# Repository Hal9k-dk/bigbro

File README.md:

# BigBro

BigBro is the system used by Hal9K to control access to its different advanced
machines, with RFID based access control.

The system is designed to cut power to the machines if no valid key-card is present
or in the special case of a 3D printer, if no special key-card is present, 
and a print isn't ongoing.

The first version of BigBro was designed around the ESP8266, specifically the WEMOS D1 mini.
Version 2 uses ESP32 with the [EspressIf ESP-IDF](https://idf.espressif.com/).

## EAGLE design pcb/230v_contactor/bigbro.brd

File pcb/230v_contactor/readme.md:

# Contactor PCB
PCB design for the normal big-bro access boxes, meant to control a 230v contactor.

Eagle version 7.2.0

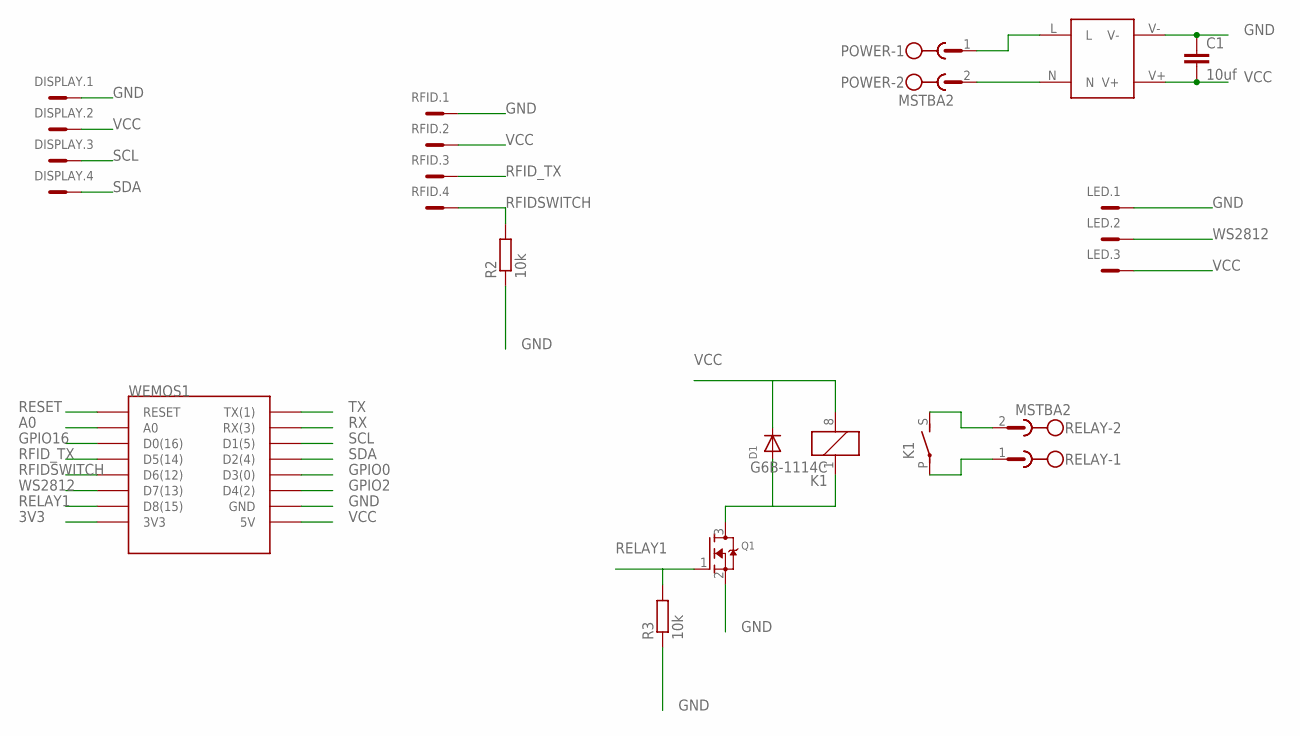
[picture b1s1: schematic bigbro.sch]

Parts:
C1: 10uf; C0805
D1: DIODESMA; SMADIODE
DISPLAY: MC4
K1: G6B-1114C
LED: MC3
POWER: MSTBA2
Q1: MOSFET-NREFLOW; SOT23
R2, R3: 10k; M0805
RELAY: MSTBA2
RFID: MC4
U$1: HLK-PM03
WEMOS1: WEMOS-D1-MINI

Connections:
3V3: WEMOS1.3V3
A0: WEMOS1.A0
GND: C1.1, DISPLAY.1, LED.1, Q1.2 (S), R2.1, R3.1, RFID.1, U$1.V-, WEMOS1.GND
GPIO0: WEMOS1.D3 (D3(0))
GPIO2: WEMOS1.D4 (D4(2))
GPIO16: WEMOS1.D0 (D0(16))
unnamed: POWER.1, U$1.L
unnamed: POWER.2, U$1.N
unnamed: K1.S, RELAY.2
unnamed: K1.P, RELAY.1
unnamed: D1.A, K1.1, Q1.3 (D)
RELAY1: Q1.1 (G), R3.2, WEMOS1.D8 (D8(15))
RESET: WEMOS1.RESET
RFIDSWITCH: R2.2, RFID.4, WEMOS1.D6 (D6(12))
RFID_TX: RFID.3, WEMOS1.D5 (D5(14))
RX: WEMOS1.RX (RX(3))
SCL: DISPLAY.3, WEMOS1.D1 (D1(5))
SDA: DISPLAY.4, WEMOS1.D2 (D2(4))
TX: WEMOS1.TX (TX(1))
VCC: C1.2, D1.C, DISPLAY.2, K1.8 (2), LED.3, RFID.2, U$1.V+, WEMOS1.5V
WS2812: LED.2, WEMOS1.D7 (D7(13))

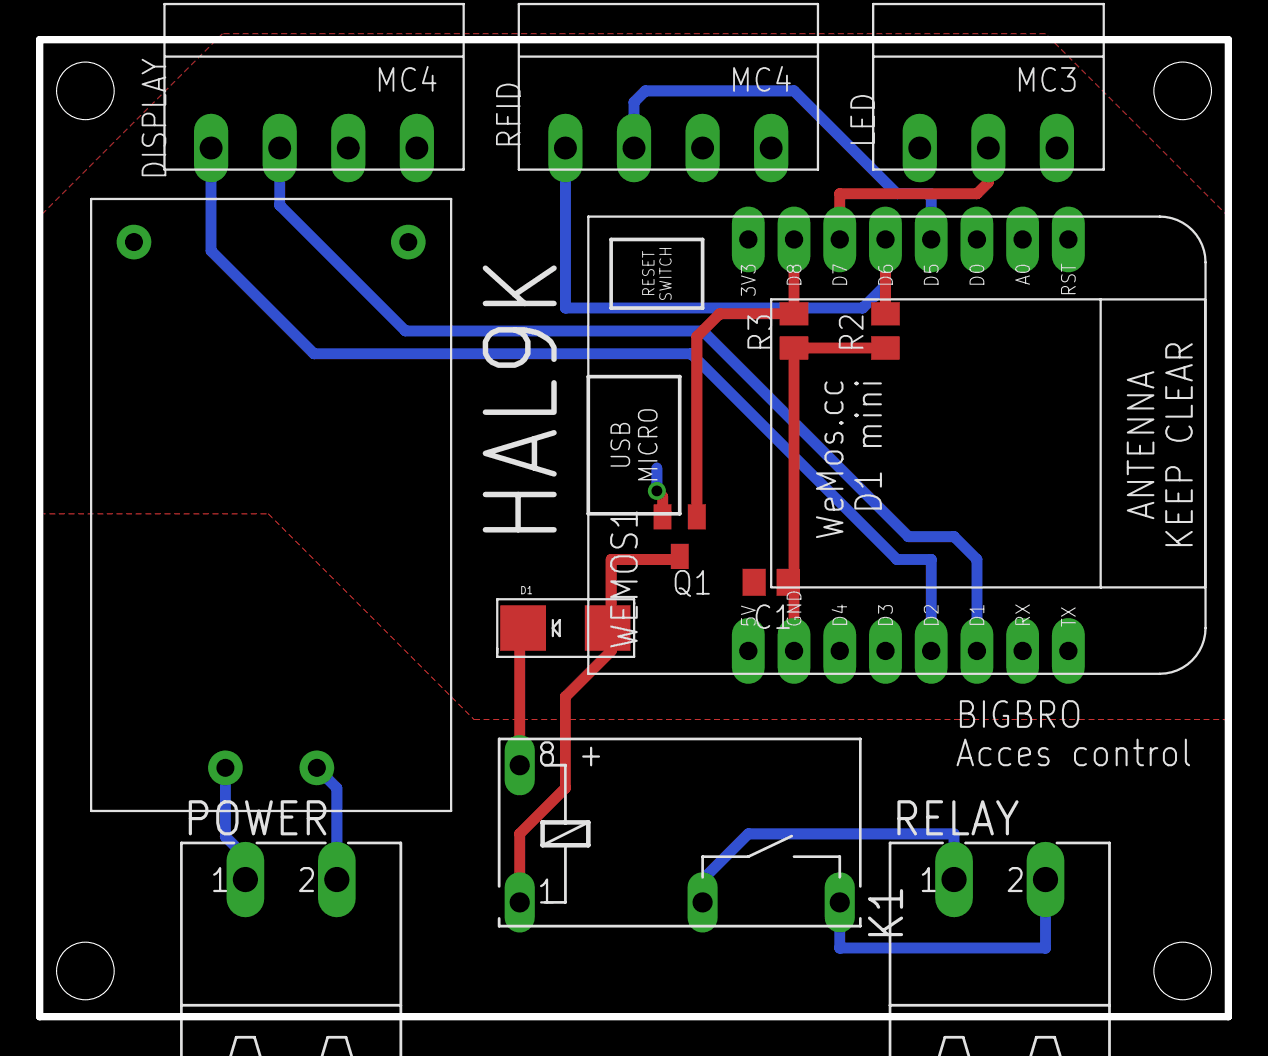
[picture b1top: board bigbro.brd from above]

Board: 2 copper layers, 66.0 x 54.3 mm, 13 parts (0 on the bottom side), 13 nets.

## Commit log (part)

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2018-09-15 firmware is currently weirdly broken
2018-09-15 First encounter of issues
2018-09-15 Further reduced complexity to get no interrupts
2018-09-16 further reduced test
2018-09-22 Changed tx pin to unused, as it is
2018-09-22 fixed current init
2018-09-22 More friendly screen
2018-09-23 Only check cards, not empty, for permission
2018-09-25 Streamlined wifi serial UI
2018-09-25 moved includes to header, added testing IP flag
2018-09-25 Moved to average of p2p current reading
2018-09-25 Added aditional input checks to wifi deltion
2018-09-25 minor changes
2018-09-25 Changed version to version 0.2.0
2018-09-27 enable travis ci
2018-09-27 Added newline after badge
2018-09-27 changed .travis.yml
2018-09-29 Began adding documentation
    Added doxygen config file.
    Documented main.cpp and base.h.
2018-09-29 Removed old .travis.yml
2018-09-29 Fixed Travis CI badge
    Capitalized read me file name.
2018-09-30 Added a bit of delay to show error messages on display
2018-09-30 Enabled more compiler warnings
2018-09-30 Moved flag test into header
2018-09-30 Removed averaging of current, reduced threshhold to 50mA
2018-09-30 Fixed lib_deps error
2018-10-18 Added threshhold for Ultimaker and TAZ
2018-10-18 Shit is broke
2018-10-18 made a temporary always on hack untill we can fix the stuff
2018-10-19 Revert "Shit is broke"
    This reverts commit e61f9288106303296d63b82bd6558d5188ae119d.
2018-10-19 Revert "Added threshhold for Ultimaker and TAZ"
    This reverts commit 2d10c56e86b93f1f911e7a29bbcce90c5f9df7a9.
2018-10-19 Made status line selection 0 indexed
2018-10-19 Cleaned up display, fixed inrush-current state change
2018-10-19 Incremented version, added options to dissable/enable ota
2018-10-19 Changed password for ota
2018-10-19 Increased cooldown to 9 minutes. Dissabled OTA during prints and cooldown
2018-10-19 something
2018-10-25 Fix UTF-8 display.
2018-10-31 Merged Access-System repo, into bigbro
2018-10-31 Fixed power-monitor PCB, to match real-life fixes
2018-12-10 made a state_change function to change state
2018-12-10 stored current_user_id
2018-12-10 Removed unused functions
2019-03-07 Worked on issue 8, pinned ArduinoJson to v5
2019-03-07 changed submodule to fork
2019-03-07 Implemented issue 8 fix
2019-03-07 Change to new submodule
2019-03-08 Made some values more human readable
2019-03-08 Merged changes from issue8 branch
2019-03-09 added threshhold configuration to platformio.ini
2019-03-09 Added "last user" field to eeprom
2019-03-09 made name_trunc a protected global. Cleaned up includes
2019-03-09 cleaned up includes
2019-03-09 made a "state_change" function to handle state changes
2019-03-09 Fixed potential EEPROM overflow issue
2019-03-09 Updated power_monitor pcb to use IRM-02 PSU
2019-03-09 Added folder for other PCB design
2019-03-09 Eagle files uploaded
2019-03-10 Pinned all libraries to major revision
2019-03-11 Removed submodule
2019-03-11 Moved to using PIO library for restclient
2019-03-13 Fixed library name
2019-03-13 Added build-flag to disable OTA, set SERIAL_DBG to 0 as default
2019-03-13 Trying to run CI on all controller types
2019-03-13 Set run to verbose for this test
2019-03-13 Added pragmas
2019-03-13 Added more pragma
2019-03-13 Disabled verbose output
2019-03-13 Only build platformio, and cancel builds if only docs changed
2019-03-13 Changed doc file to check new travis script
2019-03-13 Fixed spelling mistake
2019-03-15 added "clear" function Sets buffer to threshhold. So any new readings either screw the average up or down.
2019-03-15 Changed threshhold fr the UM
2019-03-15 Fixed printer thinking it was printing for the first minute
2019-03-15 Added super verbose serial dbg
2019-03-15 Set ota pwd to default. OTA will be disabled in production units
2019-03-15 Fixed inrush prevention function
2019-03-15 Finished up new printer code
2019-03-19 Documented Printer and ACS class
2019-03-19 Set up automated doxygen build and deployment to gh-pages
2019-03-19 Moved to much cleaner documentation generation
2019-03-19 fixed deployment branch
2019-03-19 Implemented main page for doxygen
2019-03-19 Updated main page formatting
2019-03-19 Fixed some variable descriptions
2019-03-19 More documentation
2019-03-20 Moved to single 'set_lines' function in display class
2019-09-05 A lot of stuff I can't remember, and fastled rate limit
2019-10-25 Cleanup.
2019-10-25 Bump REST client version.
2019-10-28 Add debug functions, fix peak-to-peak calculation.
2019-10-28 Add debug.
2019-10-28 Revert debug.
2019-11-28 Clear status when card is removed.
2019-11-28 while -> if
2020-01-30 Reduce debug noise.
2020-02-06 Untabify.
2020-02-06 Add lots of info in the display, make a bunch of gratuitous changes.
2020-02-06 Fix conflicts.
2020-02-06 Deploy Hal9k-dk/bigbro to github.com/Hal9k-dk/bigbro.git:gh-pages
2021-10-11 Added v2 schematic
2021-10-11 Added resistive divider to RX0
2021-10-17 Moved to SPDT relay, added 24pin FPC for e-ink
2021-10-17 Widened isolation slot
2021-10-21 Order1
2022-09-01 Add files via upload
    var begyndt på skift til andet display 1,44"
    https://www.aliexpress.com/item/4000219159401.html?spm=a2g0o.order_list.0.0.4b8d1802SihISr
2023-03-23 Add from zip file.
2023-03-30 Remove unneeded pulldown.
2023-04-01 Add local libs/footprints. Add GND testpoint.
2023-04-01 Update README for V2.
2023-04-01 Change to RDM6300, etc.
2023-04-02 New fuse holder, rearrange footprints.
2023-04-02 Optimize allocation of gates.
2023-04-02 Change current sense to single pin.
2023-04-03 Add 3D model for RDM6300 socket.
2023-04-03 Add 3D model for fuse holder.
2023-04-03 Route flip-flop, reduce width to 100 mm.
2023-04-03 Finish routing.
2023-04-03 Add extension connector.
2023-04-03 Fill zones.
2023-04-04 Remove solder mask on high-current traces.
2023-04-04 Add 3D model.
2023-04-04 Clarify connector labels.
2023-04-04 Order.
2023-05-06 Improve debug connector labels.
2023-05-06 Move display backlight from GPIO12 to GPIO14 to fix boot problem.
2023-05-06 Add reset and boot switches.
2023-05-06 Add ESP32 skeleton code.
2023-05-06 Add console interface.
2023-05-06 Add voltage divider for RFID.
2023-05-06 Increase value of switch LED resistor.
2023-05-06 Add command to read switch; initialize switch GPIO.
2023-05-13 Add simple HW test program.
2023-05-13 Add symbolic names.
2023-05-13 Use RDM6300 protocol.
2023-05-13 Make rfid command work.
2023-05-13 Add RFID pin.
2023-05-13 Add delay.
2023-05-13 Enable display CS.
2023-05-13 Flip display connector.
2023-05-14 Swap S and D on Q3.
2023-05-14 Forgot to save
2023-05-15 Connect to WiFi.
2023-05-18 Make WiFi code work.
2023-06-01 PoC for coil holder.
2023-06-01 PoC for switch holder.
2023-06-02 Adjust to fit.
2023-06-03 Adjust.
2023-06-15 Fix Q3 footprint, Q4 resistor values.
2023-06-15 Use PWM for display backlight.
2023-06-17 Tweak.
2023-06-17 Control backlight manually.
2023-06-28 Add case front.
2023-07-02 Achieve perfection.
2023-07-02 First attempt of front.
2023-07-03 Enlarge card pocket slightly.
2023-07-03 First attempt.
2023-07-03 Fix bugs.
2023-07-04 Increase width of switch opening.
2023-07-04 Basic bottom.
2023-07-04 Add PCB standoffs.
2024-02-04 Tweak; add wall fittings.
2024-02-04 Update ESP-IDF.
2024-02-04 Move.
2024-02-04 Remove old OpenSCAD files.
2024-02-05 Remove unused function.
2024-02-05 Tweak insert hole.
2024-02-09 Fix display clip position.
2024-02-09 Make display retainers a bit smaller.
2024-02-14 Copy lots of stuff from ACS frontend.
2024-02-14 Add more test commands.
2024-02-16 Add GW credentials.
2024-02-17 Implement controller FSA.
2024-02-17 Start implementing display class.
2024-02-19 Switch to new display driver.
2024-02-20 More work on display class.
2024-02-24 Finish basic display functionality.
2024-02-25 Fix bug where first progress line was lost.
2024-02-25 Turn backlight on.
2024-02-25 Fix backlight config.
2024-02-25 Implement time display.
2024-03-15 Fix time display.
2024-03-16 Work on controller logic.
2024-03-16 Fix display bugs.
2024-03-16 Always trust the cache.
2024-03-16 Show user name.
2024-03-16 Use small font for user name.
2024-03-24 Add RTS pullup.
2024-08-04 Add OTA FWU support.
2024-08-04 Cosmetic updates.
2024-09-06 Thicker.
2024-09-06 Fix too little room for switch.
2024-09-07 Add support for horizontal orientation.
2024-09-07 Reduce insert size slightly.
2024-09-15 Add PDF
2024-09-15 Add schematic.
2024-10-05 Fix bug where screw holes are offset.
2024-10-05 Special version.
2024-10-11 Reduce insert radius.
2024-10-18 Strain relief for cable.
2024-10-31 Add C6.
2024-11-04 Show identifier on boot.
2024-11-04 Do OTA check before starting threads.
2024-11-04 Fix ident display.
2024-11-07 Reduce log noise.
2024-11-07 Extend logger test.
2024-11-07 Clean up logging.
2024-11-28 Change C3 to 0608.
2024-12-25 Add WiFi indicator.
2024-12-28 Do not show 'Unknown' with no card ID.
2024-12-29 Use v3 of the API to allow handling 'no access' scenario.
2024-12-29 Initialize ADC channel, adjust messages.
2024-12-29 Add thermal pad.
2024-12-29 Updates.
2024-12-30 KiCad 9.
2024-12-30 Use a smaller fuse.
2024-12-31 Make countersink deeper.
2025-02-22 Add extra transistor.
2025-02-22 Route.
2025-02-24 Start adding JLCPCB part numbers.
2025-02-27 Add stencil.
2025-03-04 Improve debug, remove unused struct member, fix deprecations.
2025-03-13 Implement scheduled reboot.
2025-03-20 Update stencil.
2025-03-20 Enlarge ESP32 pads.
2025-03-21 Use another filename for firmware for V2 HW.
2025-04-20 Update display config, etc.
2025-04-20 Remove solder mask from relay traces.
2025-04-21 Force update if BOOT is pressed.
2025-04-21 Add resistor divider for current sense input.
2025-04-21 Start adding support for current sensor.
2025-05-01 Use zener.
2025-06-04 Add current sense task.
2025-06-04 Fix display issues.
2025-06-04 Use interrupt for current sensor.
2025-06-05 Remove return code check for esp_event_handler_unregister().
2025-07-13 Refactor.
2025-07-13 Implement current sense mode.
2025-07-14 Holder for WCS1x00 current sensor module.
2025-07-14 Bottom with cutouts for plugs.
2025-07-15 Add cutouts for retaining clips.
2025-07-29 Rename.
2025-08-01 Add holes on left side.
2025-08-02 Reduce insert hole size.
2025-10-17 ESP-IDF 5.5.1.
2025-11-20 Require three keypresses to enter debug mode.
2026-05-28 Update for ESP-IDF 6. Add MQTT support.
2026-05-28 Bump.
2026-05-30 Fix debug mode check.
2026-05-30 Disable cert check.
2026-05-30 Fix debug mode check, for real. Disable OTA check if EXT1 is pulled low.
2026-05-30 Add pin defs.
2026-05-30 Remove unneeded transistors and resistors.
2026-06-05 Revert "Disable cert check."
    This reverts commit b48e8d643a94ec2915a7033f8de10bf629965834.
2026-06-13 Enable pullup on EXT pins.
2026-06-13 Convert to MQTT.
2026-06-13 Reduce code size.
2026-06-13 Disable OTA FWU if card switch is active.
2026-06-13 Sync with v2.
2026-06-19 Simplify debug circuitry.
2026-06-19 Add power LEDs.
2026-06-28 Update scripts
2026-06-28 Align version number with HW revision.
2026-06-30 Include card_present in MQTT status.
